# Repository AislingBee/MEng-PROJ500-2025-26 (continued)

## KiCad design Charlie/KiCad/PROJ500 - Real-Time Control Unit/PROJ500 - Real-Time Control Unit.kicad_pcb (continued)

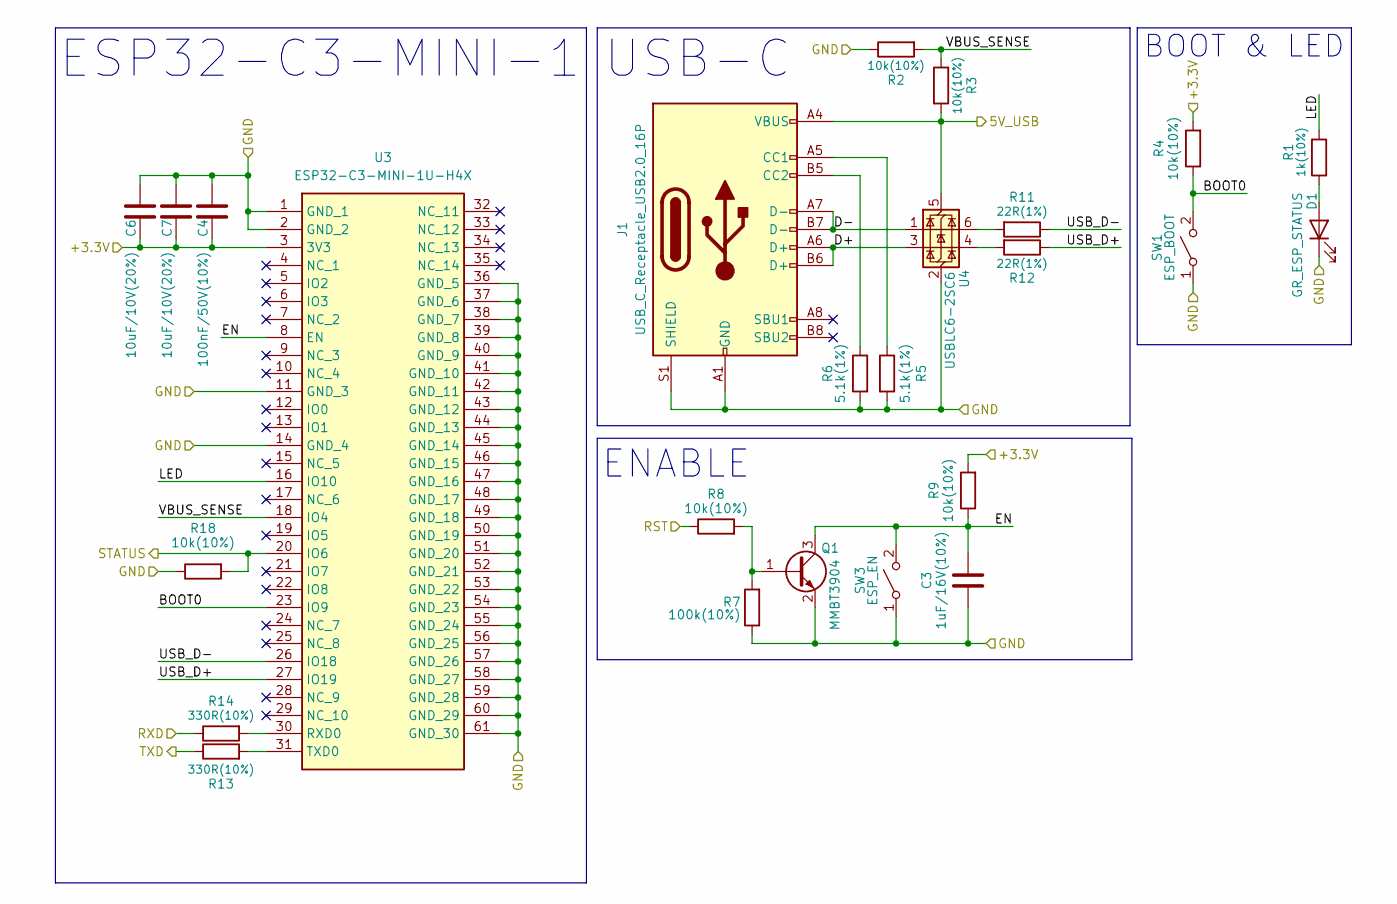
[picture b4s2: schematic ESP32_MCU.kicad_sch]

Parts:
C3: 1uF/16V(10%); C_0603_1608Metric
C4: 100nF/50V(10%); C_0402_1005Metric
C6, C7: 10uF/10V(20%); C_0603_1608Metric
D1: GR_ESP_STATUS; D_0805_2012Metric
J1: USB_C_Receptacle_USB2.0_16P; USB_C_Receptacle_GCT_USB4105-xx-A_16P_TopMnt_Horizontal
Q1: MMBT3904; SOT-23
R1: 1k(10%); R_0402_1005Metric
R2, R3, R4, R8, R9, R18: 10k(10%); R_0402_1005Metric
R5, R6: 5.1k(1%); R_0402_1005Metric
R7: 100k(10%); R_0402_1005Metric
R11, R12: 22R(1%); R_0402_1005Metric
R13, R14: 330R(10%); R_0402_1005Metric
SW1: ESP_BOOT; SW_SPST_TS-1088-xR020
SW3: ESP_EN; SW_SPST_TS-1088-xR020
U3: ESP32-C3-MINI-1U-H4X; ESP32C3MINI1UH4X; Manufacturer_Part_Number ESP32-C3-MINI-1U-H4X
U4: USBLC6-2SC6; SOT-23-6

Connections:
+3.3V: C4.1, C6.1, C7.1, R4.2, R9.2, U3.3 (3V3); also elsewhere on the board
/5V_USB: J1.A4 (VBUS), J1.A9 (VBUS), J1.B4 (VBUS), J1.B9 (VBUS), R3.2, U4.5 (VBUS); also elsewhere on the board
/ESP32 MCU/BOOT0: R4.1, SW1.2 (B), U3.23 (IO9)
/ESP32 MCU/D+: J1.A6 (D+), J1.B6 (D+), U4.3 (I/O2)
/ESP32 MCU/D-: J1.A7 (D-), J1.B7 (D-), U4.1 (I/O1)
/ESP32 MCU/EN: C3.2, Q1.3 (C), R9.1, SW3.2 (B), U3.8 (EN)
/ESP32 MCU/LED: R1.2, U3.16 (IO10)
/ESP32 MCU/USB_D+: R12.1, U3.27 (IO19)
/ESP32 MCU/USB_D-: R11.1, U3.26 (IO18)
/ESP32 MCU/VBUS_SENSE: R2.2, R3.1, U3.18 (IO4)
/ESP_RST: R8.1; also elsewhere on the board
/ESP_RXD: R14.1; also elsewhere on the board
/ESP_STATUS: R18.2, U3.20 (IO6); also elsewhere on the board
/ESP_TXD: R13.1; also elsewhere on the board
GND: C3.1, C4.2, C6.2, C7.2, D1.1 (K), J1.A1 (GND), J1.A12 (GND), J1.B1 (GND), J1.B12 (GND), J1.S1 (SHIELD), Q1.2 (E), R2.1, R5.2, R6.2, R7.1, R18.1, SW1.1 (A), SW3.1 (A), U3.1 (GND_1), U3.2 (GND_2), U3.11 (GND_3), U3.14 (GND_4), U3.36 (GND_5), U3.37 (GND_6), U3.38 (GND_7), U3.39 (GND_8), U3.40 (GND_9), U3.41 (GND_10), U3.42 (GND_11), U3.43 (GND_12), U3.44 (GND_13), U3.45 (GND_14), U3.46 (GND_15), U3.47 (GND_16), U3.48 (GND_17), U3.49 (GND_18), U3.50 (GND_19), U3.51 (GND_20), U3.52 (GND_21), U3.53 (GND_22), U3.54 (GND_23), U3.55 (GND_24), U3.56 (GND_25), U3.57 (GND_26), U3.58 (GND_27), U3.59 (GND_28), U3.60 (GND_29), U3.61 (GND_30), U4.2 (GND); also elsewhere on the board
unnamed: D1.2 (A), R1.1
unnamed: J1.A5 (CC1), R5.1
unnamed: J1.B5 (CC2), R6.1
unnamed: Q1.1 (B), R7.2, R8.2
unnamed: R11.2, U4.6 (I/O1)
unnamed: R12.2, U4.4 (I/O2)
unnamed: R14.2, U3.30 (RXD0)
unnamed: R13.2, U3.31 (TXD0)

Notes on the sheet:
ENABLE
ESP32-C3-MINI-1
USB-C
BOOT & LED

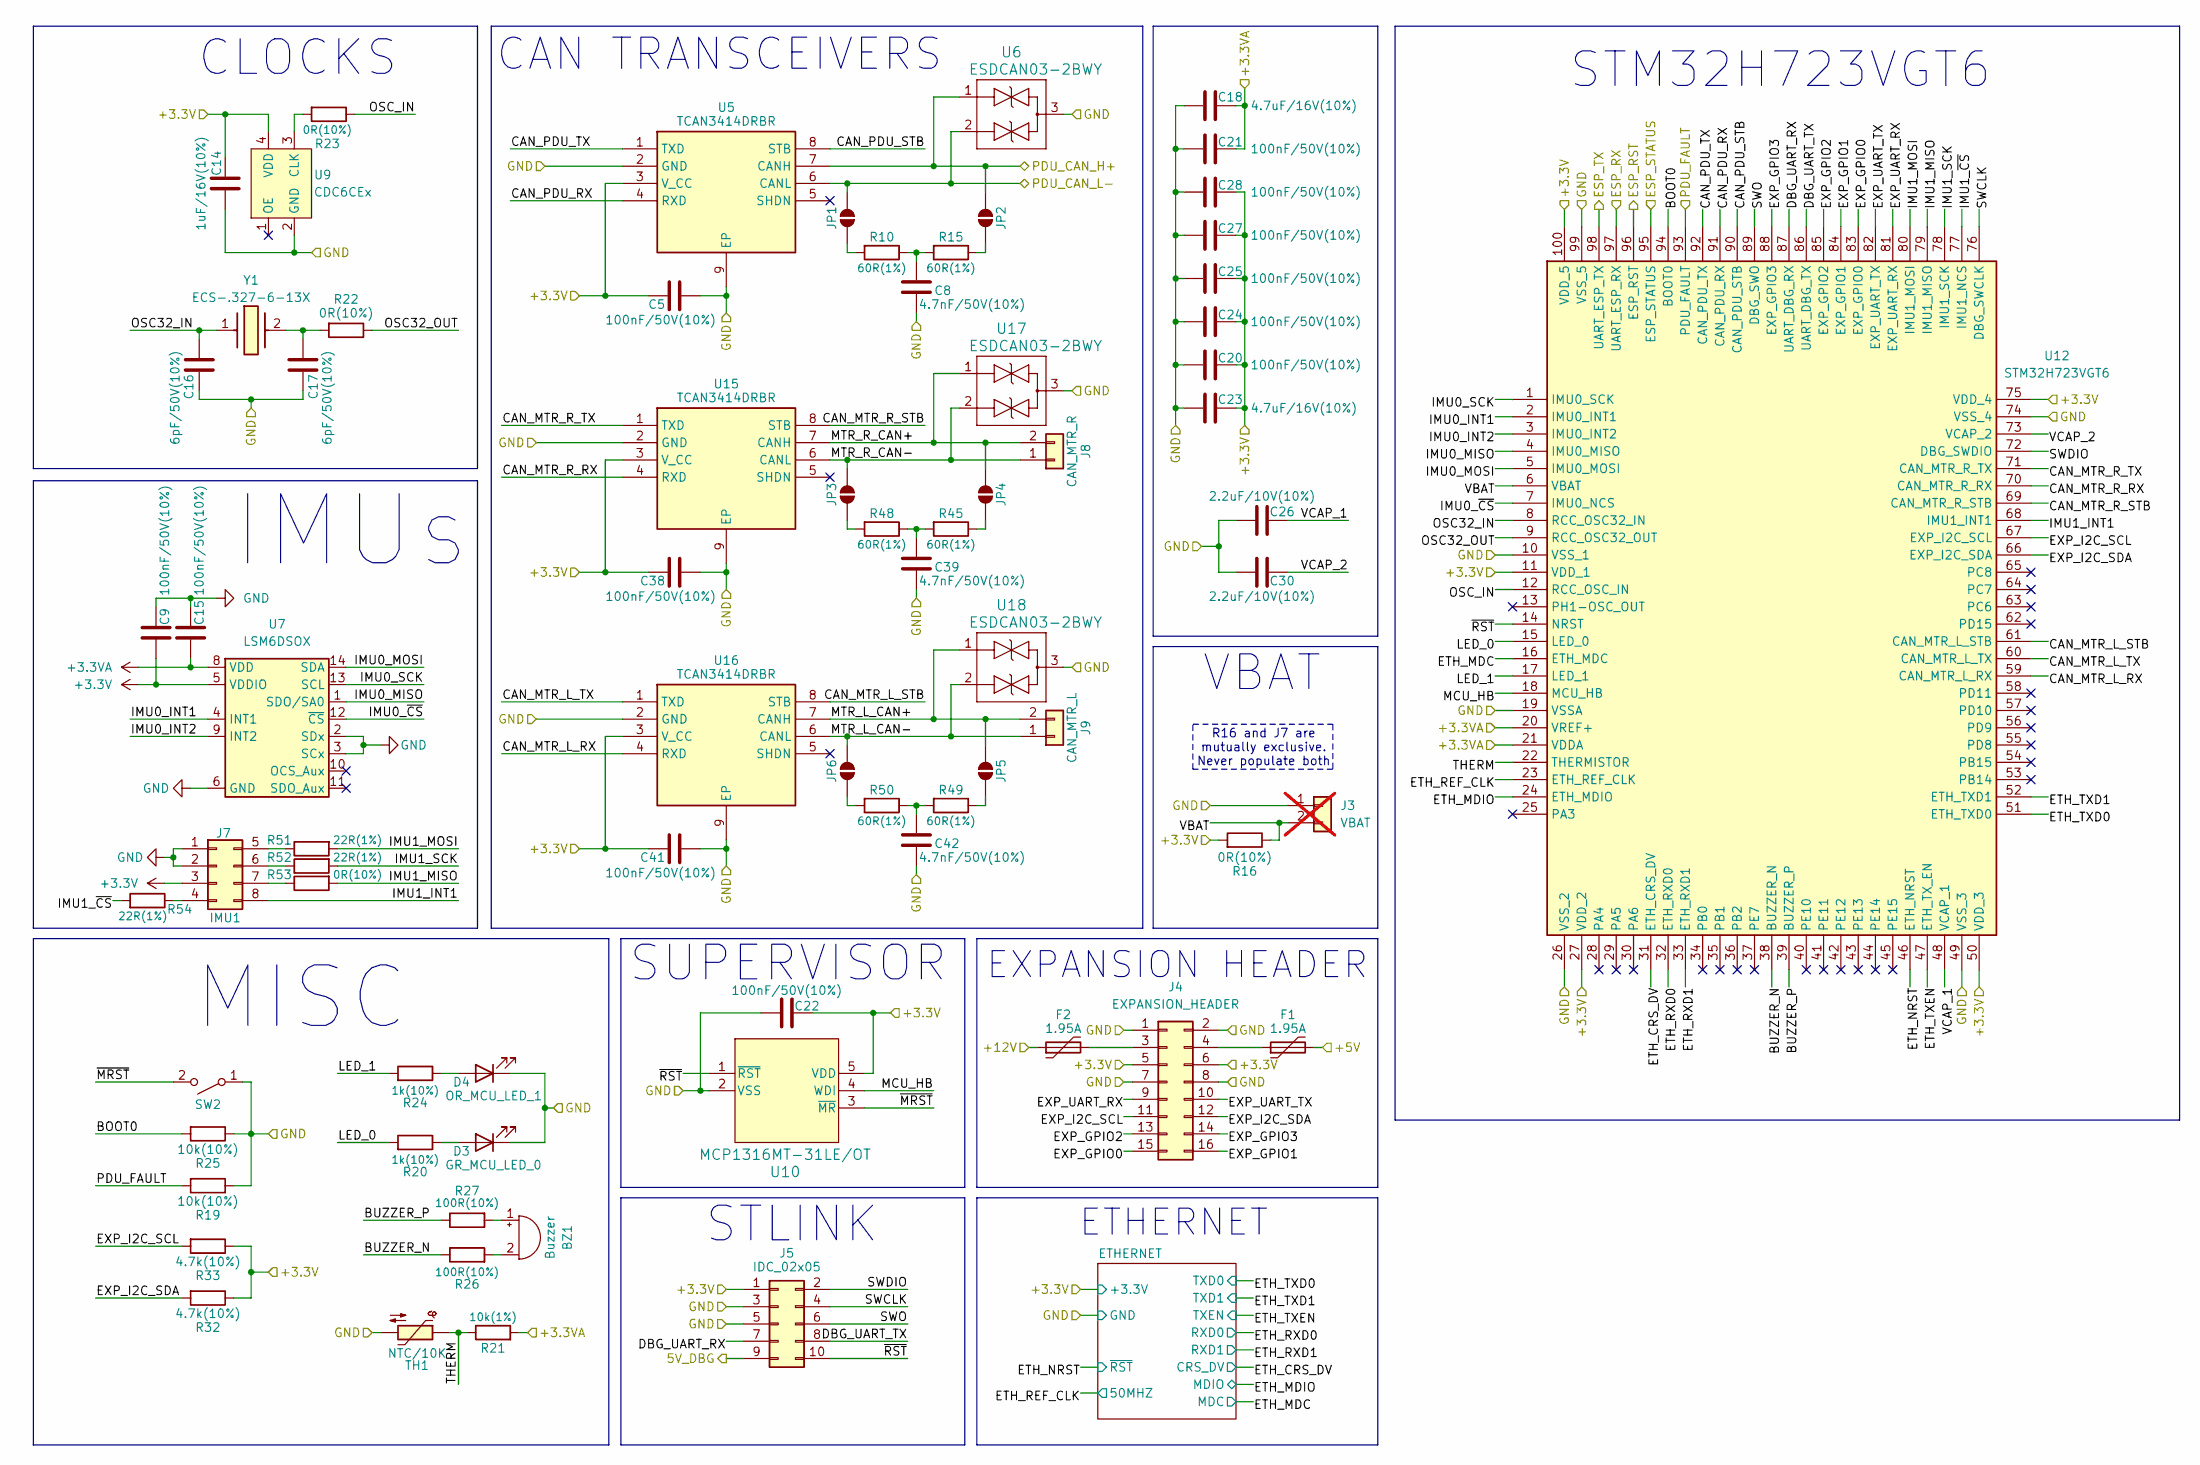
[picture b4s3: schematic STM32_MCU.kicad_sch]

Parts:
BZ1: Buzzer; C_Radial_D10.0mm_H12.5mm_P5.00mm
C5, C9, C15, C20, C21, C22, C24, C25, C27, C28, C38, C41: 100nF/50V(10%); C_0402_1005Metric
C8, C39, C42: 4.7nF/50V(10%); C_0402_1005Metric
C14: 1uF/16V(10%); C_0603_1608Metric
C16, C17: 6pF/50V(10%); C_0402_1005Metric
C18, C23: 4.7uF/16V(10%); C_0805_2012Metric
C26, C30: 2.2uF/10V(10%); C_0603_1608Metric
D3: GR_MCU_LED_0; D_0805_2012Metric
D4: OR_MCU_LED_1; D_0805_2012Metric
F1, F2: 1.95A; FUSC4632X200N
J3: VBAT; PinHeader_1x02_P2.54mm_Vertical; Part Number 1-0201FBV0T; not fitted
J4: EXPANSION_HEADER; IDC-Header_2x08_P2.54mm_Vertical
J5: IDC_02x05; IDC-Header_2x05_P2.54mm_Vertical
J7: IMU1; Molex_Micro-Fit_3.0_43045-0800_2x04_P3.00mm_Horizontal
J8: CAN_MTR_R; Molex_Micro-Fit_3.0_43045-0200_2x01_P3.00mm_Horizontal
J9: CAN_MTR_L; Molex_Micro-Fit_3.0_43045-0200_2x01_P3.00mm_Horizontal
JP1, JP2, JP3, JP4, JP5, JP6: SolderJumper_2_Open; SolderJumper-2_P1.3mm_Open_Pad1.0x1.5mm
R10, R15, R45, R48, R49, R50: 60R(1%); R_0402_1005Metric
R16, R22, R23, R53: 0R(10%); R_0402_1005Metric
R19, R25: 10k(10%); R_0402_1005Metric
R20, R24: 1k(10%); R_0402_1005Metric
R21: 10k(1%); R_0402_1005Metric
R26, R27: 100R(10%); R_0402_1005Metric
R32, R33: 4.7k(10%); R_0402_1005Metric
R51, R52, R54: 22R(1%); R_0402_1005Metric
SW2: SW_SPST; SW_SPST_TS-1088-xR020
TH1: NTC/10K; R_0402_1005Metric
U5, U15, U16: TCAN3414DRBR; VSON-8-1EP_3x3mm_P0.65mm_EP1.6x2.4mm; Mouser Part Number 595-TCAN3414DRBR
U6, U17, U18: ESDCAN03-2BWY; SOT-323_SC-70
U7: LSM6DSOX; ST_LGA-14L_2.5x3.0mm_P0.5mm_4x3
U9: CDC6CEx; Oscillator_SMD_VSON-4_2x1.6mm
U10: MCP1316MT-31LE/OT; SOT-23-5
U12: STM32H723VGT6; LQFP-100_14x14mm_P0.5mm
Y1: ECS-.327-6-13X; Crystal_DS26_D2.0mm_L6.0mm_Vertical; Mouser Part Number 520-ECS327-6-13-X

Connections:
+3.3V: C5.2, C9.1, C14.1, C20.2, C22.1, C23.1, C24.2, C25.2, C27.2, C28.2, C38.2, C41.2, J4.5, J4.6, J5.1, J7.3, R16.2, R32.1, R33.1, U5.3 (V_CC), U7.5 (VDDIO), U9.4 (VDD), U10.5 (VDD), U12.11 (VDD_1), U12.27 (VDD_2), U12.50 (VDD_3), U12.75 (VDD_4), U12.100 (VDD_5), U15.3 (V_CC), U16.3 (V_CC); also elsewhere on the board
+3.3VA: C15.1, C18.1, C21.2, R21.2, U7.8 (VDD), U12.20 (VREF+), U12.21 (VDDA); also elsewhere on the board
+5V: F1.2; also elsewhere on the board
+12V: F2.1; also elsewhere on the board
/5V_DBG: J5.9; also elsewhere on the board
/ESP_RST: U12.96 (ESP_RST); also elsewhere on the board
/ESP_RXD: U12.98 (UART_ESP_TX); also elsewhere on the board
/ESP_STATUS: U12.95 (ESP_STATUS); also elsewhere on the board
/ESP_TXD: U12.97 (UART_ESP_RX); also elsewhere on the board
/PDU_CAN+: JP2.2 (B), U5.7 (CANH), U6.1; also elsewhere on the board
/PDU_CAN-: JP1.2 (B), U5.6 (CANL), U6.2; also elsewhere on the board
/PDU_FAULT: R19.2, U12.93 (PDU_FAULT); also elsewhere on the board
/STM32 MCU/BOOT0: R25.2, U12.94 (BOOT0)
/STM32 MCU/BUZZER_N: R26.1, U12.38 (BUZZER_N)
/STM32 MCU/BUZZER_P: R27.1, U12.39 (BUZZER_P)
/STM32 MCU/CAN_MTR_L_RX: U12.59 (CAN_MTR_L_RX), U16.4 (RXD)
/STM32 MCU/CAN_MTR_L_STB: U12.61 (CAN_MTR_L_STB), U16.8 (STB)
/STM32 MCU/CAN_MTR_L_TX: U12.60 (CAN_MTR_L_TX), U16.1 (TXD)
/STM32 MCU/CAN_MTR_R_RX: U12.70 (CAN_MTR_R_RX), U15.4 (RXD)
/STM32 MCU/CAN_MTR_R_STB: U12.69 (CAN_MTR_R_STB), U15.8 (STB)
/STM32 MCU/CAN_MTR_R_TX: U12.71 (CAN_MTR_R_TX), U15.1 (TXD)
/STM32 MCU/CAN_PDU_RX: U5.4 (RXD), U12.91 (CAN_PDU_RX)
/STM32 MCU/CAN_PDU_STB: U5.8 (STB), U12.90 (CAN_PDU_STB)
/STM32 MCU/CAN_PDU_TX: U5.1 (TXD), U12.92 (CAN_PDU_TX)
/STM32 MCU/DBG_UART_RX: J5.7, U12.87 (UART_DBG_RX)
/STM32 MCU/DBG_UART_TX: J5.8, U12.86 (UART_DBG_TX)
/STM32 MCU/ETH_CRS_DV: U12.31 (ETH_CRS_DV); also elsewhere on the board
/STM32 MCU/ETH_MDC: U12.16 (ETH_MDC); also elsewhere on the board
/STM32 MCU/ETH_MDIO: U12.24 (ETH_MDIO); also elsewhere on the board
/STM32 MCU/ETH_NRST: U12.46 (ETH_NRST); also elsewhere on the board
/STM32 MCU/ETH_REF_CLK: U12.23 (ETH_REF_CLK); also elsewhere on the board
/STM32 MCU/ETH_RXD0: U12.32 (ETH_RXD0); also elsewhere on the board
/STM32 MCU/ETH_RXD1: U12.33 (ETH_RXD1); also elsewhere on the board
/STM32 MCU/ETH_TXD0: U12.51 (ETH_TXD0); also elsewhere on the board
/STM32 MCU/ETH_TXD1: U12.52 (ETH_TXD1); also elsewhere on the board
/STM32 MCU/ETH_TXEN: U12.47 (ETH_TX_EN); also elsewhere on the board
/STM32 MCU/EXP_GPIO0: J4.15, U12.83 (EXP_GPIO0)
/STM32 MCU/EXP_GPIO1: J4.16, U12.84 (EXP_GPIO1)
/STM32 MCU/EXP_GPIO2: J4.13, U12.85 (EXP_GPIO2)
/STM32 MCU/EXP_GPIO3: J4.14, U12.88 (EXP_GPIO3)
/STM32 MCU/EXP_I2C_SCL: J4.11, R33.2, U12.67 (EXP_I2C_SCL)
/STM32 MCU/EXP_I2C_SDA: J4.12, R32.2, U12.66 (EXP_I2C_SDA)
/STM32 MCU/EXP_UART_RX: J4.9, U12.81 (EXP_UART_RX)
/STM32 MCU/EXP_UART_TX: J4.10, U12.82 (EXP_UART_TX)
/STM32 MCU/IMU0_INT1: U7.4 (INT1), U12.2 (IMU0_INT1)
/STM32 MCU/IMU0_INT2: U7.9 (INT2), U12.3 (IMU0_INT2)
/STM32 MCU/IMU0_MISO: U7.1 (SDO/SA0), U12.4 (IMU0_MISO)
/STM32 MCU/IMU0_MOSI: U7.14 (SDA), U12.5 (IMU0_MOSI)
/STM32 MCU/IMU0_SCK: U7.13 (SCL), U12.1 (IMU0_SCK)
/STM32 MCU/IMU0_~CS: U7.12 (~CS), U12.7 (IMU0_NCS)
/STM32 MCU/IMU1_INT1: J7.8, U12.68 (IMU1_INT1)
/STM32 MCU/IMU1_MISO: R53.2, U12.79 (IMU1_MISO)
/STM32 MCU/IMU1_MOSI: R51.2, U12.80 (IMU1_MOSI)
/STM32 MCU/IMU1_SCK: R52.2, U12.78 (IMU1_SCK)
/STM32 MCU/IMU1_~CS: R54.2, U12.77 (IMU1_NCS)
/STM32 MCU/LED_0: R20.2, U12.15 (LED_0)
/STM32 MCU/LED_1: R24.2, U12.17 (LED_1)
/STM32 MCU/MCU_HB: U10.4 (WDI), U12.18 (MCU_HB)
/STM32 MCU/MTR_L_CAN+: J9.2, JP5.2 (B), U16.7 (CANH), U18.1
/STM32 MCU/MTR_L_CAN-: J9.1, JP6.2 (B), U16.6 (CANL), U18.2
/STM32 MCU/MTR_R_CAN+: J8.2, JP4.2 (B), U15.7 (CANH), U17.1
/STM32 MCU/MTR_R_CAN-: J8.1, JP3.2 (B), U15.6 (CANL), U17.2
/STM32 MCU/OSC32_IN: C16.2, U12.8 (RCC_OSC32_IN), Y1.1
/STM32 MCU/OSC32_OUT: R22.1, U12.9 (RCC_OSC32_OUT)
/STM32 MCU/OSC_IN: R23.1, U12.12 (RCC_OSC_IN)
/STM32 MCU/SWCLK: J5.4, U12.76 (DBG_SWCLK)
/STM32 MCU/SWDIO: J5.2, U12.72 (DBG_SWDIO)
/STM32 MCU/SWO: J5.6, U12.89 (DBG_SWO)
/STM32 MCU/THERM: R21.1, TH1.1, U12.22 (THERMISTOR)
/STM32 MCU/VBAT: J3.2, R16.1, U12.6 (VBAT)
/STM32 MCU/VCAP_1: C26.1, U12.48 (VCAP_1)
/STM32 MCU/VCAP_2: C30.1, U12.73 (VCAP_2)
/STM32 MCU/~MRST: SW2.2 (B), U10.3 (~MR)
/STM32 MCU/~RST: J5.10, U10.1 (~RST), U12.14 (NRST)
GND: C5.1, C8.1, C9.2, C14.2, C15.2, C16.1, C17.1, C18.2, C20.1, C21.1, C22.2, C23.2, C24.1, C25.1, C26.2, C27.1, C28.1, C30.2, C38.1, C39.1, C41.1, C42.1, D3.1 (K), D4.1 (K), J3.1, J4.1, J4.2, J4.7, J4.8, J5.3, J5.5, J7.1, J7.2, R19.1, R25.1, SW2.1 (A), TH1.2, U5.2 (GND), U5.9 (EP), U6.3, U7.2 (SDx), U7.3 (SCx), U7.6 (GND), U7.7 (GND), U9.2 (GND), U10.2 (VSS), U12.10 (VSS_1), U12.19 (VSSA), U12.26 (VSS_2), U12.49 (VSS_3), U12.74 (VSS_4), U12.99 (VSS_5), U15.2 (GND), U15.9 (EP), U16.2 (GND), U16.9 (EP), U17.3, U18.3; also elsewhere on the board
unnamed: BZ1.1 (+), R27.2
unnamed: BZ1.2 (-), R26.2
unnamed: C8.2, R10.1, R15.2
unnamed: C17.2, R22.2, Y1.2
unnamed: C39.2, R45.2, R48.1
unnamed: C42.2, R49.2, R50.1
unnamed: D3.2 (A), R20.1
unnamed: D4.2 (A), R24.1
unnamed: F2.2, J4.3
unnamed: F1.1, J4.4
unnamed: J7.4, R54.1
unnamed: J7.5, R51.1
unnamed: J7.6, R52.1
unnamed: J7.7, R53.1
unnamed: JP1.1 (A), R10.2
unnamed: JP2.1 (A), R15.1
unnamed: JP3.1 (A), R48.2
unnamed: JP4.1 (A), R45.1
unnamed: JP5.1 (A), R49.1
unnamed: JP6.1 (A), R50.2
unnamed: R23.2, U9.3 (CLK)

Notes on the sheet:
STLINK
R16 and J7 are mutually exclusive. Never populate both
ETHERNET
MISC
SUPERVISOR
STM32H723VGT6
CAN TRANSCEIVERS
EXPANSION HEADER
IMUs
CLOCKS
VBAT

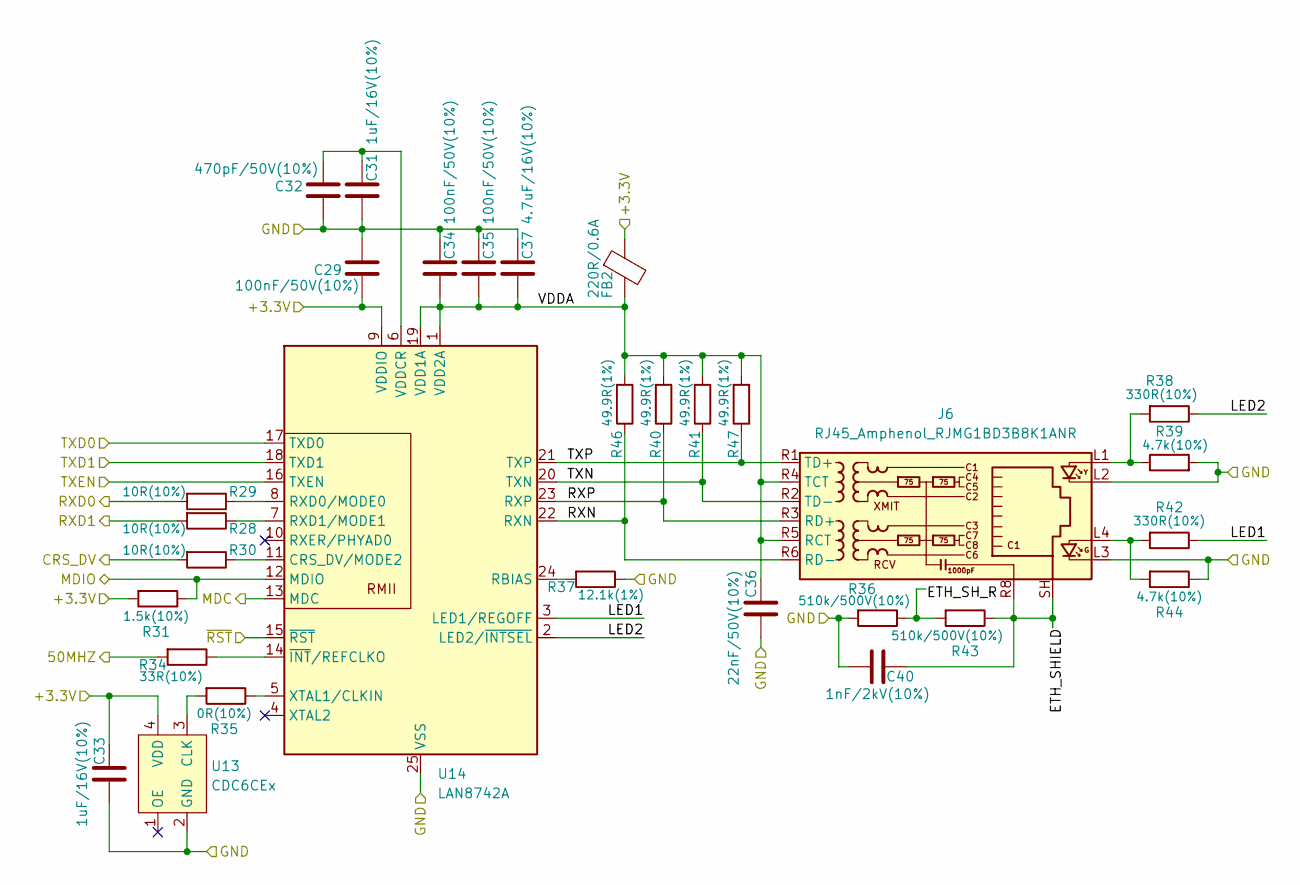
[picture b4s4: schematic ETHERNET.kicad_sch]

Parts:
C29, C34, C35: 100nF/50V(10%); C_0402_1005Metric
C31, C33: 1uF/16V(10%); C_0603_1608Metric
C32: 470pF/50V(10%); C_0402_1005Metric
C36: 22nF/50V(10%); C_0402_1005Metric
C37: 4.7uF/16V(10%); C_0805_2012Metric
C40: 1nF/2kV(10%); C_1206_3216Metric
FB2: 220R/0.6A; L_0402_1005Metric
J6: RJ45_Amphenol_RJMG1BD3B8K1ANR
R28, R29, R30: 10R(10%); R_0402_1005Metric
R31: 1.5k(10%); R_0402_1005Metric
R34: 33R(10%); R_0402_1005Metric
R35: 0R(10%); R_0402_1005Metric
R36, R43: 510k/500V(10%); R_1206_3216Metric
R37: 12.1k(1%); R_0402_1005Metric
R38, R42: 330R(10%); R_0402_1005Metric
R39, R44: 4.7k(10%); R_0402_1005Metric
R40, R41, R46, R47: 49.9R(1%); R_0402_1005Metric
U13: CDC6CEx; Oscillator_SMD_VSON-4_2x1.6mm
U14: LAN8742A; VQFN-24-1EP_4x4mm_P0.5mm_EP2.5x2.5mm

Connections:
+3.3V: C29.1, C33.1, FB2.1, R31.2, U13.4 (VDD), U14.9 (VDDIO); also elsewhere on the board
/STM32 MCU/ETHERNET/ETH_SHIELD: C40.1, J6.R8, J6.SH, R43.1
/STM32 MCU/ETHERNET/ETH_SH_R: R36.1, R43.2
/STM32 MCU/ETHERNET/LED1: R42.1, U14.3 (LED1/REGOFF)
/STM32 MCU/ETHERNET/LED2: R38.1, U14.2 (LED2/~INTSEL)
/STM32 MCU/ETHERNET/RXN: J6.R6 (RD-), R46.1, U14.22 (RXN)
/STM32 MCU/ETHERNET/RXP: J6.R3 (RD+), R40.1, U14.23 (RXP)
/STM32 MCU/ETHERNET/TXN: J6.R2 (TD-), R41.1, U14.20 (TXN)
/STM32 MCU/ETHERNET/TXP: J6.R1 (TD+), R47.1, U14.21 (TXP)
/STM32 MCU/ETHERNET/VDDA: C34.1, C35.1, C36.1, C37.1, FB2.2, J6.R4 (TCT), J6.R5 (RCT), R40.2, R41.2, R46.2, R47.2, U14.1 (VDD2A), U14.19 (VDD1A)
/STM32 MCU/ETH_CRS_DV: R30.2; also elsewhere on the board
/STM32 MCU/ETH_MDC: U14.13 (MDC); also elsewhere on the board
/STM32 MCU/ETH_MDIO: R31.1, U14.12 (MDIO); also elsewhere on the board
/STM32 MCU/ETH_NRST: U14.15 (~RST); also elsewhere on the board
/STM32 MCU/ETH_REF_CLK: R34.2; also elsewhere on the board
/STM32 MCU/ETH_RXD0: R29.2; also elsewhere on the board
/STM32 MCU/ETH_RXD1: R28.2; also elsewhere on the board
/STM32 MCU/ETH_TXD0: U14.17 (TXD0); also elsewhere on the board
/STM32 MCU/ETH_TXD1: U14.18 (TXD1); also elsewhere on the board
/STM32 MCU/ETH_TXEN: U14.16 (TXEN); also elsewhere on the board
GND: C29.2, C31.1, C32.1, C33.2, C34.2, C35.2, C36.2, C37.2, C40.2, J6.L2, J6.L3, R36.2, R37.1, R39.2, R44.1, U13.2 (GND), U14.25 (VSS); also elsewhere on the board
unnamed: J6.L1, R38.2, R39.1
unnamed: J6.L4, R42.2, R44.2
unnamed: R35.2, U13.3 (CLK)
unnamed: R30.1, U14.11 (CRS_DV/MODE2)
unnamed: R37.2, U14.24 (RBIAS)
unnamed: R29.1, U14.8 (RXD0/MODE0)
unnamed: R28.1, U14.7 (RXD1/MODE1)
unnamed: C31.2, C32.2, U14.6 (VDDCR)
unnamed: R35.1, U14.5 (XTAL1/CLKIN)
unnamed: R34.1, U14.14 (~INT/REFCLKO)

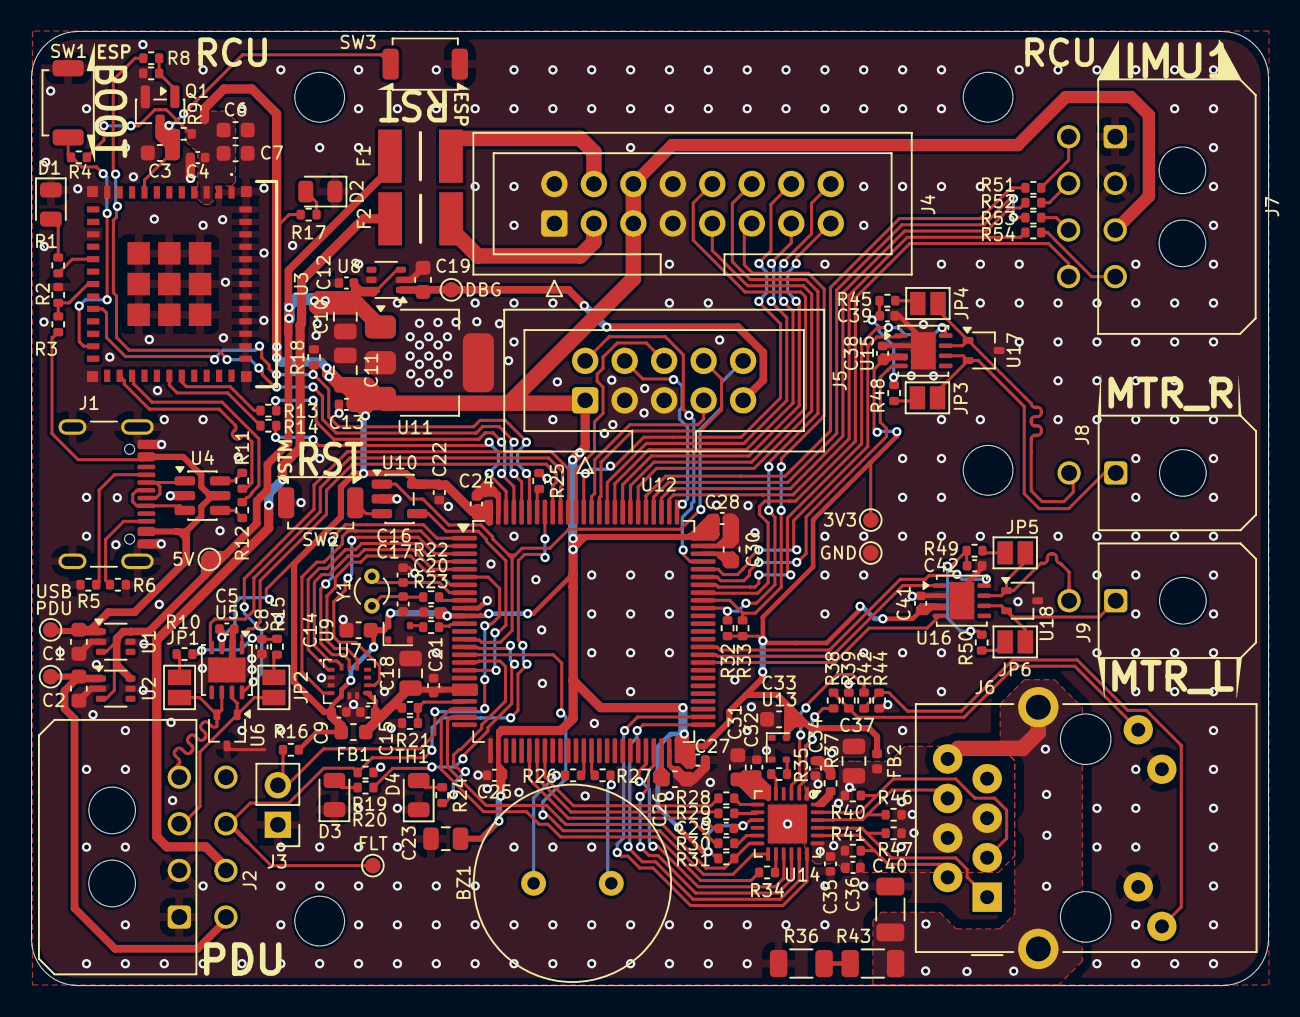
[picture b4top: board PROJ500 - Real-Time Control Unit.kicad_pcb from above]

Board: 2 copper layers, 79.6 x 61.4 mm, 155 parts (0 on the bottom side), 134 nets.

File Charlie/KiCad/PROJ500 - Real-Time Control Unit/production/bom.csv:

Designator,Footprint,Quantity,Value,LCSC Part #
BZ1,C_Radial_D10.0mm_H12.5mm_P5.00mm,1,Buzzer,
"C1, C14, C19, C2, C3, C31, C33",0603,7,1uF/16V(10%),
"C10, C11, C18, C23, C37",0805,5,4.7uF/16V(10%),
"C12, C13, C15, C20, C21, C22, C24, C25, C27, C28, C29, C34, C35, C38, C4, C41, C5, C9",0402,18,100nF/50V(10%),
"C16, C17",0402,2,6pF/50V(10%),
"C26, C30",0603,2,2.2uF/10V(10%),
C32,0402,1,470pF/50V(10%),
C36,0402,1,22nF/50V(10%),
"C39, C42, C8",0402,3,4.7nF/50V(10%),
C40,1206,1,1nF/2kV(10%),
"C6, C7",0603,2,10uF/10V(20%),
D1,0805,1,GR_ESP_STATUS,
D2,0805,1,GR_PWR,
D3,0805,1,GR_MCU_LED_0,
D4,0805,1,OR_MCU_LED_1,
"F1, F2",FUSC4632X200N,2,1.95A,
FB1,0603,1,120R/3A,
FB2,0402,1,220R/0.6A,
J1,USB_C_Receptacle_GCT_USB4105-xx-A_16P_TopMnt_Horizontal,1,USB_C_Receptacle_USB2.0_16P,
J2,Molex_Micro-Fit_3.0_43045-0800_2x04_P3.00mm_Horizontal,1,RCU_B2B,
J4,IDC-Header_2x08_P2.54mm_Vertical,1,EXPANSION_HEADER,
J5,IDC-Header_2x05_P2.54mm_Vertical,1,IDC_02x05,
J6,RJ45_Amphenol_RJMG1BD3B8K1ANR,1,RJ45_Amphenol_RJMG1BD3B8K1ANR,
J7,Molex_Micro-Fit_3.0_43045-0800_2x04_P3.00mm_Horizontal,1,IMU1,
J8,Molex_Micro-Fit_3.0_43045-0200_2x01_P3.00mm_Horizontal,1,CAN_MTR_R,
J9,Molex_Micro-Fit_3.0_43045-0200_2x01_P3.00mm_Horizontal,1,CAN_MTR_L,
Q1,SOT-23,1,MMBT3904,
"R1, R17, R20, R24",0402,4,1k(10%),
"R10, R15, R45, R48, R49, R50",0402,6,60R(1%),
"R11, R12, R51, R52, R54",0402,5,22R(1%),
"R13, R14, R38, R42",0402,4,330R(10%),
"R16, R22, R23, R35, R53",0402,5,0R(10%),
"R18, R19, R2, R25, R3, R4, R8, R9",0402,8,10k(10%),
R21,0402,1,10k(1%),
"R26, R27",0402,2,100R(10%),
"R28, R29, R30",0402,3,10R(10%),
R31,0402,1,1.5k(10%),
"R32, R33, R39, R44",0402,4,4.7k(10%),
R34,0402,1,33R(10%),
"R36, R43",1206,2,510k/500V(10%),
R37,0402,1,12.1k(1%),
"R40, R41, R46, R47",0402,4,49.9R(1%),
"R5, R6",0402,2,5.1k(1%),
R7,0402,1,100k(10%),
SW1,SW_SPST_TS-1088-xR020,1,ESP_BOOT,
SW2,SW_SPST_TS-1088-xR020,1,SW_SPST,
SW3,SW_SPST_TS-1088-xR020,1,ESP_EN,
TH1,0402,1,NTC/10K,
"TP1, TP2, TP3, TP4, TP5, TP6, TP7",TestPoint_Pad_D1.0mm,7,TestPoint,
"U1, U2, U8",SOT-363_SC-70-6,3,LM66100DCK,
U10,SOT-23-5,1,MCP1316MT-31LE/OT,
U11,SOT-223,1,AP2114HA-3.3TRG1,
U12,LQFP-100_14x14mm_P0.5mm,1,STM32H723VGT6,
"U13, U9",Oscillator_SMD_VSON-4_2x1.6mm,2,CDC6CEx,
U14,VQFN-24-1EP_4x4mm_P0.5mm_EP2.5x2.5mm,1,LAN8742A,
"U15, U16, U5",VSON-8-1EP_3x3mm_P0.65mm_EP1.6x2.4mm,3,TCAN3414DRBR,
"U17, U18, U6",SOT-323_SC-70,3,ESDCAN03-2BWY,
U3,ESP32C3MINI1UH4X,1,ESP32-C3-MINI-1U-H4X,
U4,SOT-23-6,1,USBLC6-2SC6,
U7,ST_LGA-14L_2.5x3.0mm_P0.5mm_4x3,1,LSM6DSOX,
Y1,Crystal_DS26_D2.0mm_L6.0mm_Vertical,1,ECS-.327-6-13X,

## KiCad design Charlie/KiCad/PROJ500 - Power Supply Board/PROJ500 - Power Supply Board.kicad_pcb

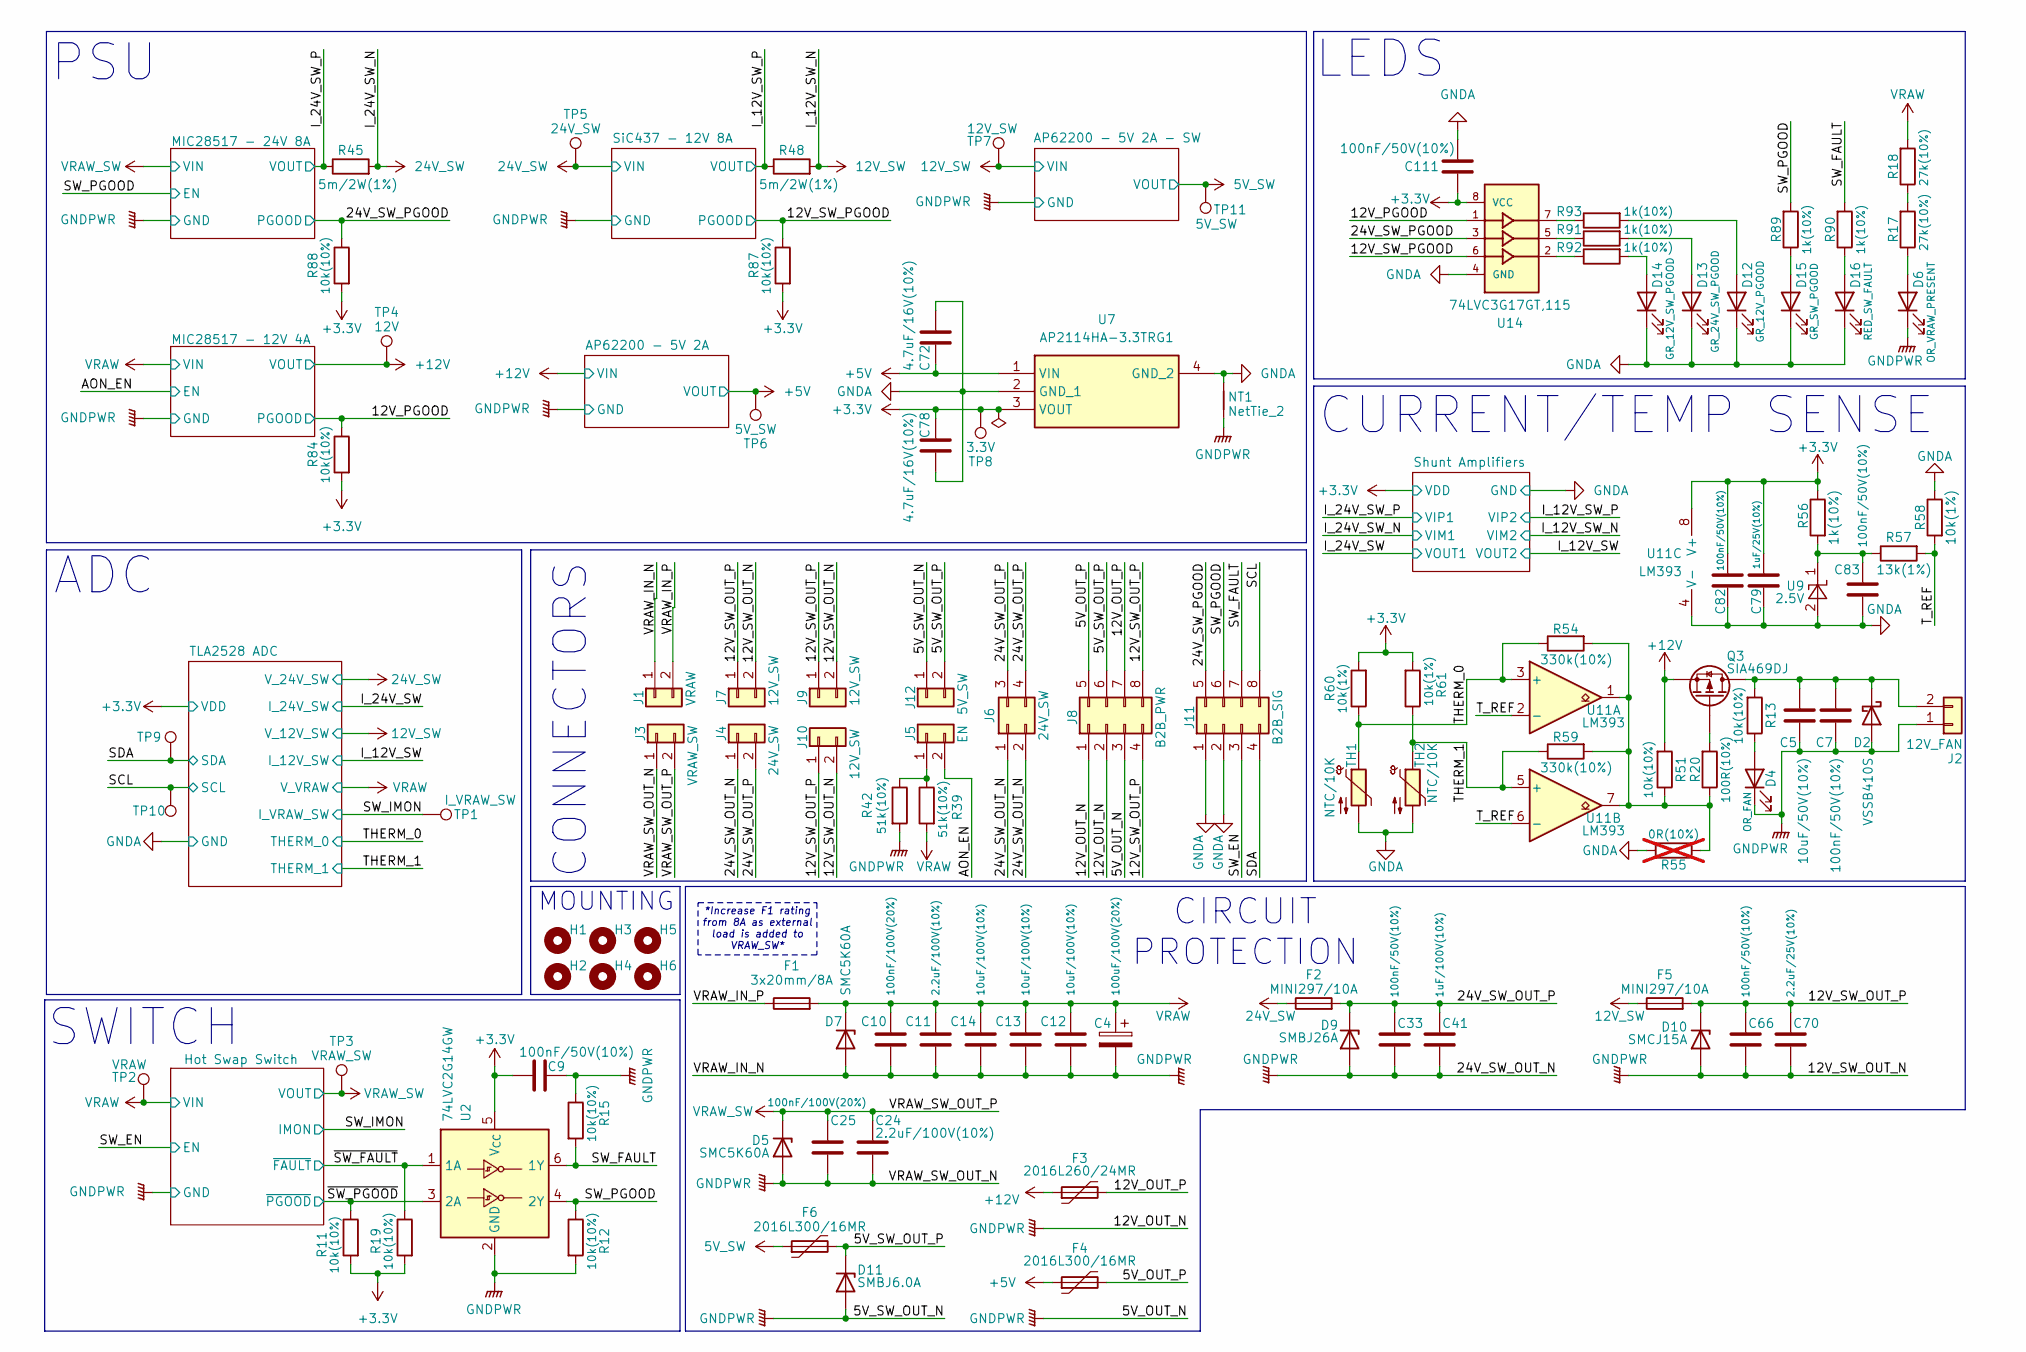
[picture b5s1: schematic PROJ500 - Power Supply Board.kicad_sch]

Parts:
C4: 100uF/100V(20%); CP_Radial_D10.0mm_P5.00mm
C5: 10uF/50V(10%); C_1206_3216Metric
C7, C9, C33, C66, C82, C83, C111: 100nF/50V(10%); C_0402_1005Metric
C10, C25: 100nF/100V(20%); C_0603_1608Metric
C11, C24: 2.2uF/100V(10%); C_0805_2012Metric
C12, C13, C14: 10uF/100V(10%); C_1210_3225Metric
C41: 1uF/100V(10%); C_0603_1608Metric
C70: 2.2uF/25V(10%); C_0805_2012Metric
C72, C78: 4.7uF/16V(10%); C_0805_2012Metric
C79: 1uF/25V(10%); C_0603_1608Metric
D2: VSSB410S; D_SMB
D4: OR_FAN; D_0805_2012Metric
D5, D7: SMC5K60A; D_SMC
D6: OR_VRAW_PRESENT; D_0805_2012Metric
D9: SMBJ26A; D_SMB
D10: SMCJ15A; D_SMC
D11: SMBJ6.0A; D_SMB
D12: GR_12V_PGOOD; D_0805_2012Metric
D13: GR_24V_SW_PGOOD; D_0805_2012Metric
D14: GR_12V_SW_PGOOD; D_0805_2012Metric
D15: GR_SW_PGOOD; D_0805_2012Metric
D16: RED_SW_FAULT; D_0805_2012Metric
F1: 3x20mm/8A; 65600301009
F2, F5: MINI297/10A; Fuseholder_Blade_Mini_Keystone_3568
F3: 2016L260/24MR; FUSC5141X160N
F4, F6: 2016L300/16MR; FUSC5141X160N
H1, H2, H3, H4, H5, H6: MountingHole; MountingHole_3.2mm_M3
J1: VRAW; AMASS_XT30PW-M_1x02_P2.50mm_Horizontal
J2: 12V_FAN; Molex_Micro-Fit_3.0_43045-0200_2x01_P3.00mm_Horizontal
J3: VRAW_SW; AMASS_XT30PW-F_1x02_P2.50mm_Horizontal
J4: 24V_SW; TBP02R138102BE
J5: EN; Molex_Micro-Fit_3.0_43045-0200_2x01_P3.00mm_Horizontal
J6: 24V_SW; Molex_Micro-Fit_3.0_43045-0400_2x02_P3.00mm_Horizontal
J7: 12V_SW; Molex_Micro-Fit_3.0_43045-0200_2x01_P3.00mm_Horizontal
J8: B2B_PWR; Molex_Micro-Fit_3.0_43045-0800_2x04_P3.00mm_Horizontal
J9, J10: 12V_SW; TBP02R138102BE
J11: B2B_SIG; Molex_Micro-Fit_3.0_43045-0800_2x04_P3.00mm_Horizontal
J12: 5V_SW; TBP02R138102BE
NT1: NetTie_2; NetTie-2_SMD_Pad0.5mm
Q3: SIA469DJ; SIA469DJT1GE3
R11, R12, R13, R15, R19, R51, R84, R87, R88: 10k(10%); R_0402_1005Metric
R17, R18: 27k(10%); R_0402_1005Metric
R20: 100R(10%); R_0402_1005Metric
R39, R42: 51k(10%); R_0402_1005Metric
R45, R48: 5m/2W(1%); R_2512_6332Metric
R54, R59: 330k(10%); R_0402_1005Metric
R55: 0R(10%); R_0402_1005Metric; not fitted
R56, R89, R90, R91, R92, R93: 1k(10%); R_0402_1005Metric
R57: 13k(1%); R_0402_1005Metric
R58, R60, R61: 10k(1%); R_0402_1005Metric
TH1, TH2: NTC/10K; R_0402_1005Metric
TP1: I_VRAW_SW; TestPoint_Pad_D1.0mm
TP2: VRAW; TestPoint_Pad_D1.0mm
TP3: VRAW_SW; TestPoint_Pad_D1.0mm
TP4: 12V; TestPoint_Pad_D1.0mm
TP5: 24V_SW; TestPoint_Pad_D1.0mm
TP6, TP11: 5V_SW; TestPoint_Pad_D1.0mm
TP7: 12V_SW; TestPoint_Pad_D1.0mm
TP8: 3.3V; TestPoint_Pad_D1.0mm
TP9: SDA; TestPoint_Pad_D1.0mm
TP10: SCL; TestPoint_Pad_D1.0mm
U2: 74LVC2G14GW; SOT-363_SC-70-6
U7: AP2114HA-3.3TRG1; SOT-223; Mouser Part Number 621-AP2114HA-3.3TRG1
U9: 2.5V; SOT-23-3; Part Number LM4040B25FTA
U11: LM393; TSSOP-8_4.4x3mm_P0.65mm
U14: 74LVC3G17GT,115; XC7WT14GT115

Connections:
5V_SW: F6.1, TP11.1; also elsewhere on the board
12V_SW: F5.1, R48.2, TP7.1; also elsewhere on the board
24V_SW: F2.1, R45.2, TP5.1; also elsewhere on the board
+3.3V: C9.1, C78.2, C79.1, C82.1, C111.2, R11.2, R19.2, R56.1, R60.2, R61.2, R84.2, R87.2, R88.2, TP8.1, U2.5 (V_{CC}), U7.3 (VOUT), U11.8 (V+), U14.8 (VCC); also elsewhere on the board
+5V: C72.2, F4.1, TP6.1, U7.1 (VIN); also elsewhere on the board
+12V: F3.1, Q3.S, R51.2, TP4.1; also elsewhere on the board
/5V_OUT_P: F4.2, J8.5
/5V_SW_OUT_P: D11.1 (K), F6.2, J8.6, J12.2
/12V_OUT_P: F3.2, J8.7
/12V_PGOOD: R84.1, U14.1; also elsewhere on the board
/12V_SW_OUT_P: C66.2, C70.2, D10.1 (K), F5.2, J7.1, J8.4, J8.8, J9.1, J10.1
/12V_SW_PGOOD: R87.1, U14.6; also elsewhere on the board
/24V_SW_OUT_P: C33.2, C41.1, D9.1 (K), F2.2, J4.2, J6.3, J6.4
/24V_SW_PGOOD: J11.5, R88.1, U14.3; also elsewhere on the board
/AON_EN: J5.2; also elsewhere on the board
/I_12V_SW_P: R48.1; also elsewhere on the board
/I_24V_SW_P: R45.1; also elsewhere on the board
/SCL: J11.8, TP10.1; also elsewhere on the board
/SDA: J11.4, TP9.1; also elsewhere on the board
/SW_EN: J11.3; also elsewhere on the board
/SW_FAULT: J11.7, R15.2, R90.2, U2.6 (1Y)
/SW_IMON: TP1.1; also elsewhere on the board
/SW_PGOOD: J11.6, R12.1, R89.2, U2.4 (2Y); also elsewhere on the board
/THERM_0: R54.1, R60.1, TH1.1, U11.3 (+); also elsewhere on the board
/THERM_1: R59.1, R61.1, TH2.1, U11.5 (+); also elsewhere on the board
/T_REF: R57.2, R58.2, U11.2 (-), U11.6 (-)
/VRAW_IN_P: F1.1, J1.2
/~SW_FAULT: R19.1, U2.1 (1A); also elsewhere on the board
/~SW_PGOOD: R11.1, U2.3 (2A); also elsewhere on the board
GNDA: C72.1, C78.1, C79.2, C82.2, C83.2, C111.1, D12.1 (K), D13.1 (K), D14.1 (K), D15.1 (K), D16.1 (K), J11.1, J11.2, NT1.2, R55.2, R58.1, TH1.2, TH2.2, U7.2 (GND_1), U7.4 (GND_2), U9.2 (A), U11.4 (V-), U14.4 (GND); also elsewhere on the board
GNDPWR: C4.2, C5.2, C7.2, C9.2, C10.1, C11.2, C12.2, C13.2, C14.2, C24.2, C25.1, C33.1, C41.2, C66.1, C70.1, D2.2 (A), D4.1 (K), D5.2 (A), D6.1 (K), D7.2 (A), D9.2 (A), D10.2 (A), D11.2 (A), J1.1, J2.1, J3.1, J4.1, J6.1, J6.2, J7.2, J8.1, J8.2, J8.3, J9.2, J10.2, J12.1, NT1.1, R12.2, R15.1, R42.2, U2.2 (GND); also elsewhere on the board
unnamed: C5.1, C7.1, D2.1 (K), J2.2, Q3.D, R13.2
unnamed: D4.2 (A), R13.1
unnamed: D6.2 (A), R17.1
unnamed: D12.2 (A), R93.2
unnamed: D13.2 (A), R91.2
unnamed: D14.2 (A), R92.2
unnamed: D15.2 (A), R89.1
unnamed: D16.2 (A), R90.1
unnamed: J5.1, R39.1, R42.1
unnamed: Q3.G, R20.2
unnamed: R17.2, R18.1
unnamed: R20.1, R51.1, R54.2, R55.1, R59.2, U11.1, U11.7
unnamed: R91.1, U14.5
unnamed: R92.1, U14.2
unnamed: R93.1, U14.7
unnamed: C83.1, R56.2, R57.1, U9.1 (K)
VRAW: C4.1, C10.2, C11.1, C12.1, C13.1, C14.1, D7.1 (K), F1.2, R18.2, R39.2, TP2.1; also elsewhere on the board
VRAW_SW: C24.1, C25.2, D5.1 (K), J3.2, TP3.1; also elsewhere on the board

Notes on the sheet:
ADC
CIRCUIT PROTECTION
*Increase F1 rating from 8A as external load is added to VRAW_SW*
SWITCH
LEDS
CURRENT/TEMP SENSE
CONNECTORS
PSU
MOUNTING
